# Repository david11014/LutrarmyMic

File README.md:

# LutrarmyMic microphone circuit

# README.md
[English README.en.md](README.en.md)

[繁體中文 README.zh-Hans.md](README.zh-Hans.md)

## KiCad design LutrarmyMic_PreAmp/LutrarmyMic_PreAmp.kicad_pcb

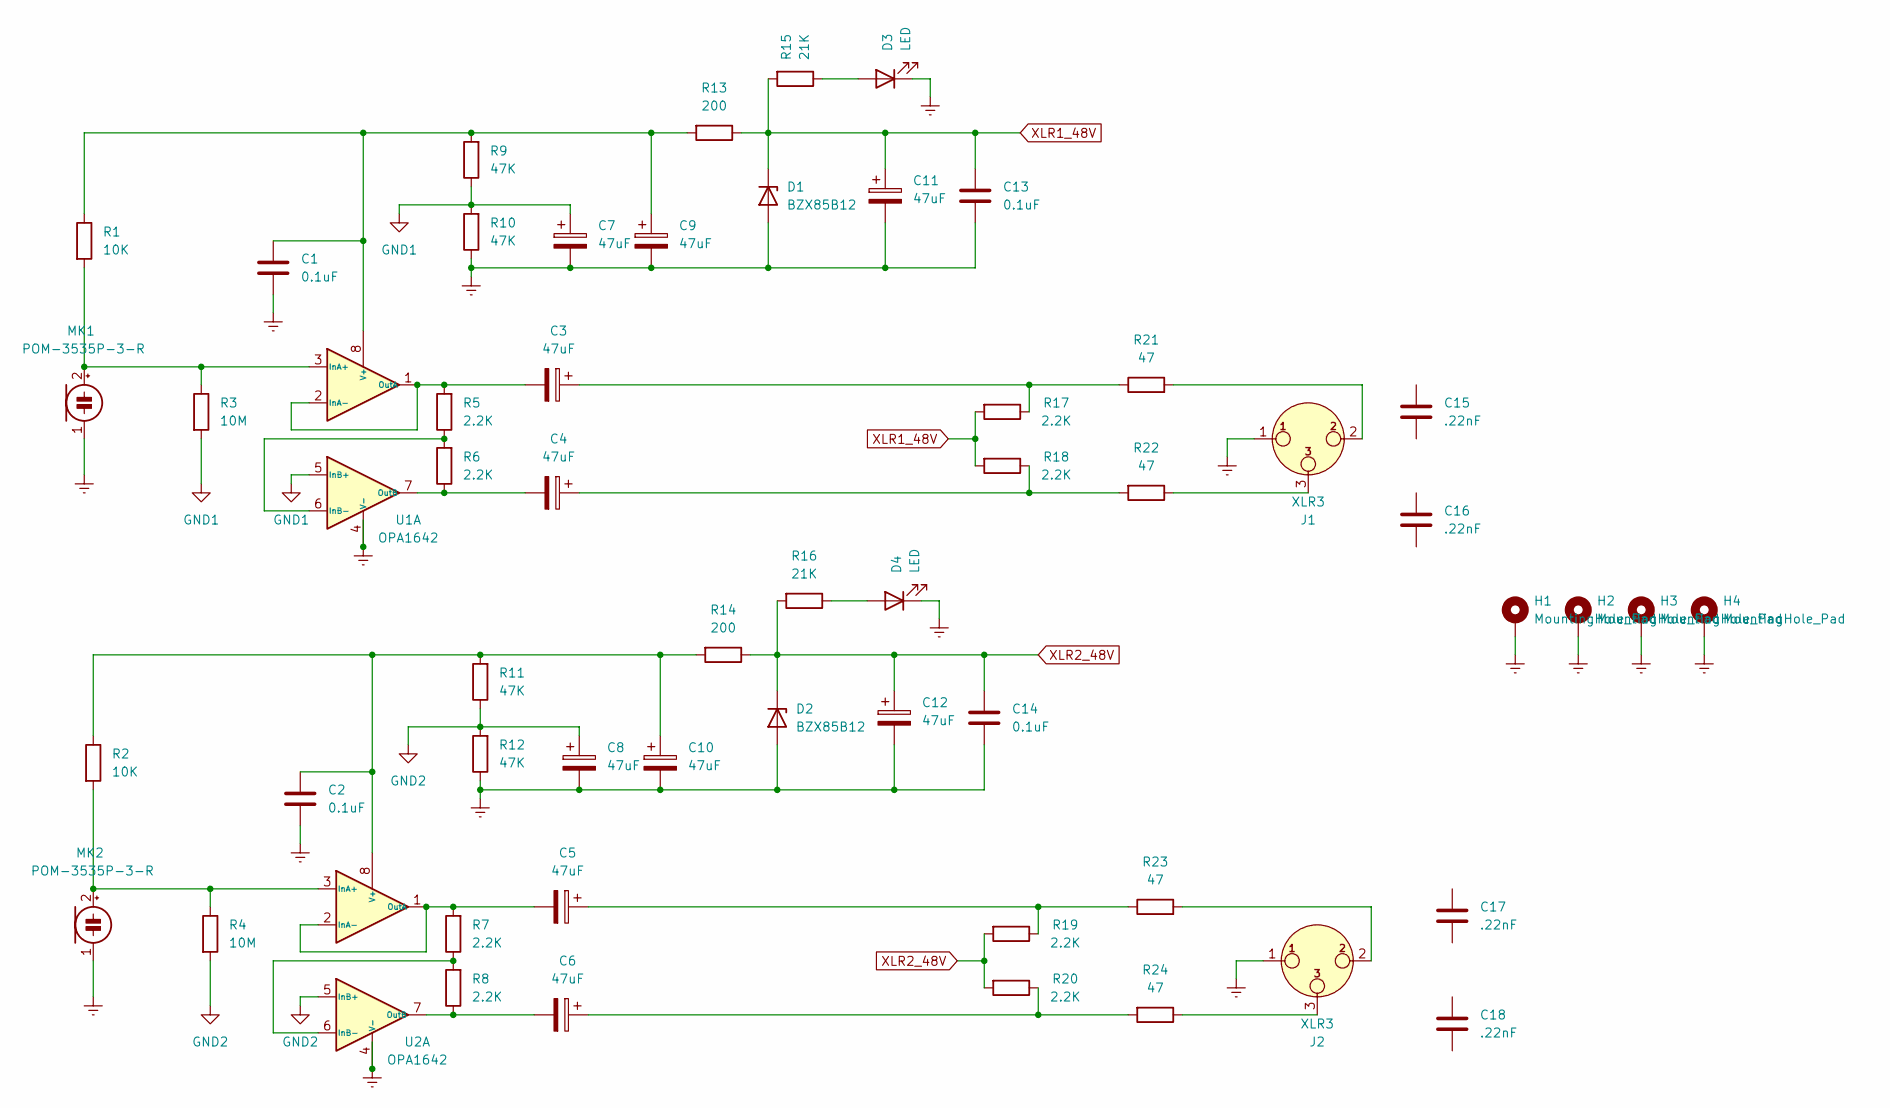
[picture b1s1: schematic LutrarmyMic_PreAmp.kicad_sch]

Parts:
C1, C2, C13, C14: 0.1uF; C_Rect_L7.2mm_W2.5mm_P5.00mm_FKS2_FKP2_MKS2_MKP2
C3, C4, C5, C6, C7, C8, C9, C10, C11, C12: 47uF; CP_Radial_D8.0mm_P3.50mm
C15, C16, C17, C18: .22nF; C_Rect_L7.2mm_W2.5mm_P5.00mm_FKS2_FKP2_MKS2_MKP2
D1, D2: BZX85B12; D_DO-41_SOD81_P10.16mm_Horizontal
D3, D4: LED; LED_D5.0mm_Clear
H1, H2, H3, H4: MountingHole_Pad; MountingHole_3.2mm_M3_DIN965_Pad
J1, J2: XLR3; PinHeader_1x03_P2.54mm_Vertical
MK1, MK2: POM-3535P-3-R; PinHeader_1x02_P2.54mm_Vertical
R1, R2: 10K; R_Axial_DIN0207_L6.3mm_D2.5mm_P10.16mm_Horizontal
R3, R4: 10M; R_Axial_DIN0207_L6.3mm_D2.5mm_P10.16mm_Horizontal
R5, R6, R7, R8, R17, R18, R19, R20: 2.2K; R_Axial_DIN0207_L6.3mm_D2.5mm_P2.54mm_Vertical
R9, R10, R11, R12: 47K; R_Axial_DIN0207_L6.3mm_D2.5mm_P2.54mm_Vertical
R13, R14: 200; R_Axial_DIN0207_L6.3mm_D2.5mm_P10.16mm_Horizontal
R15, R16: 21K; R_Axial_DIN0207_L6.3mm_D2.5mm_P10.16mm_Horizontal
R21, R22, R23, R24: 47; R_Axial_DIN0207_L6.3mm_D2.5mm_P10.16mm_Horizontal
U1, U2: OPA1642; SOIC-8_3.9x4.9mm_P1.27mm

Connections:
Earth: C1.2, C2.2, C7.2, C8.2, C9.2, C10.2, C11.2, C12.2, C13.2, C14.2, D1.2 (A), D2.2 (A), D3.1 (K), D4.1 (K), H1.1, H2.1, H3.1, H4.1, J1.1, J2.1, MK1.1 (-), MK2.1 (-), R10.1, R12.1, U1.4 (V-), U2.4 (V-)
GND1: C7.1, R3.2, R9.1, R10.2, U1.5 (InB+)
GND2: C8.1, R4.2, R11.1, R12.2, U2.5 (InB+)
unnamed: C1.1, C9.1, R1.1, R9.2, R13.2, U1.8 (V+)
unnamed: C3.1, R17.1, R21.1
unnamed: C3.2, R5.2, U1.1 (OutA), U1.2 (InA-)
unnamed: C4.1, R18.1, R22.2
unnamed: C4.2, R6.1, U1.7 (OutB)
unnamed: C5.1, R19.1, R23.1
unnamed: C5.2, R7.2, U2.1 (OutA), U2.2 (InA-)
unnamed: C6.1, R20.1, R24.2
unnamed: C6.2, R8.1, U2.7 (OutB)
unnamed: C2.1, C10.1, R2.1, R11.2, R14.2, U2.8 (V+)
unnamed: D3.2 (A), R15.1
unnamed: D4.2 (A), R16.1
unnamed: J1.2, R21.2
unnamed: J1.3, R22.1
unnamed: J2.2, R23.2
unnamed: J2.3, R24.1
unnamed: MK1.2 (+), R1.2, R3.1, U1.3 (InA+)
unnamed: MK2.2 (+), R2.2, R4.1, U2.3 (InA+)
unnamed: R5.1, R6.2, U1.6 (InB-)
unnamed: R7.1, R8.2, U2.6 (InB-)
XLR1_48V: C11.1, C13.1, D1.1 (K), R13.1, R15.2, R17.2, R18.2
XLR2_48V: C12.1, C14.1, D2.1 (K), R14.1, R16.2, R19.2, R20.2

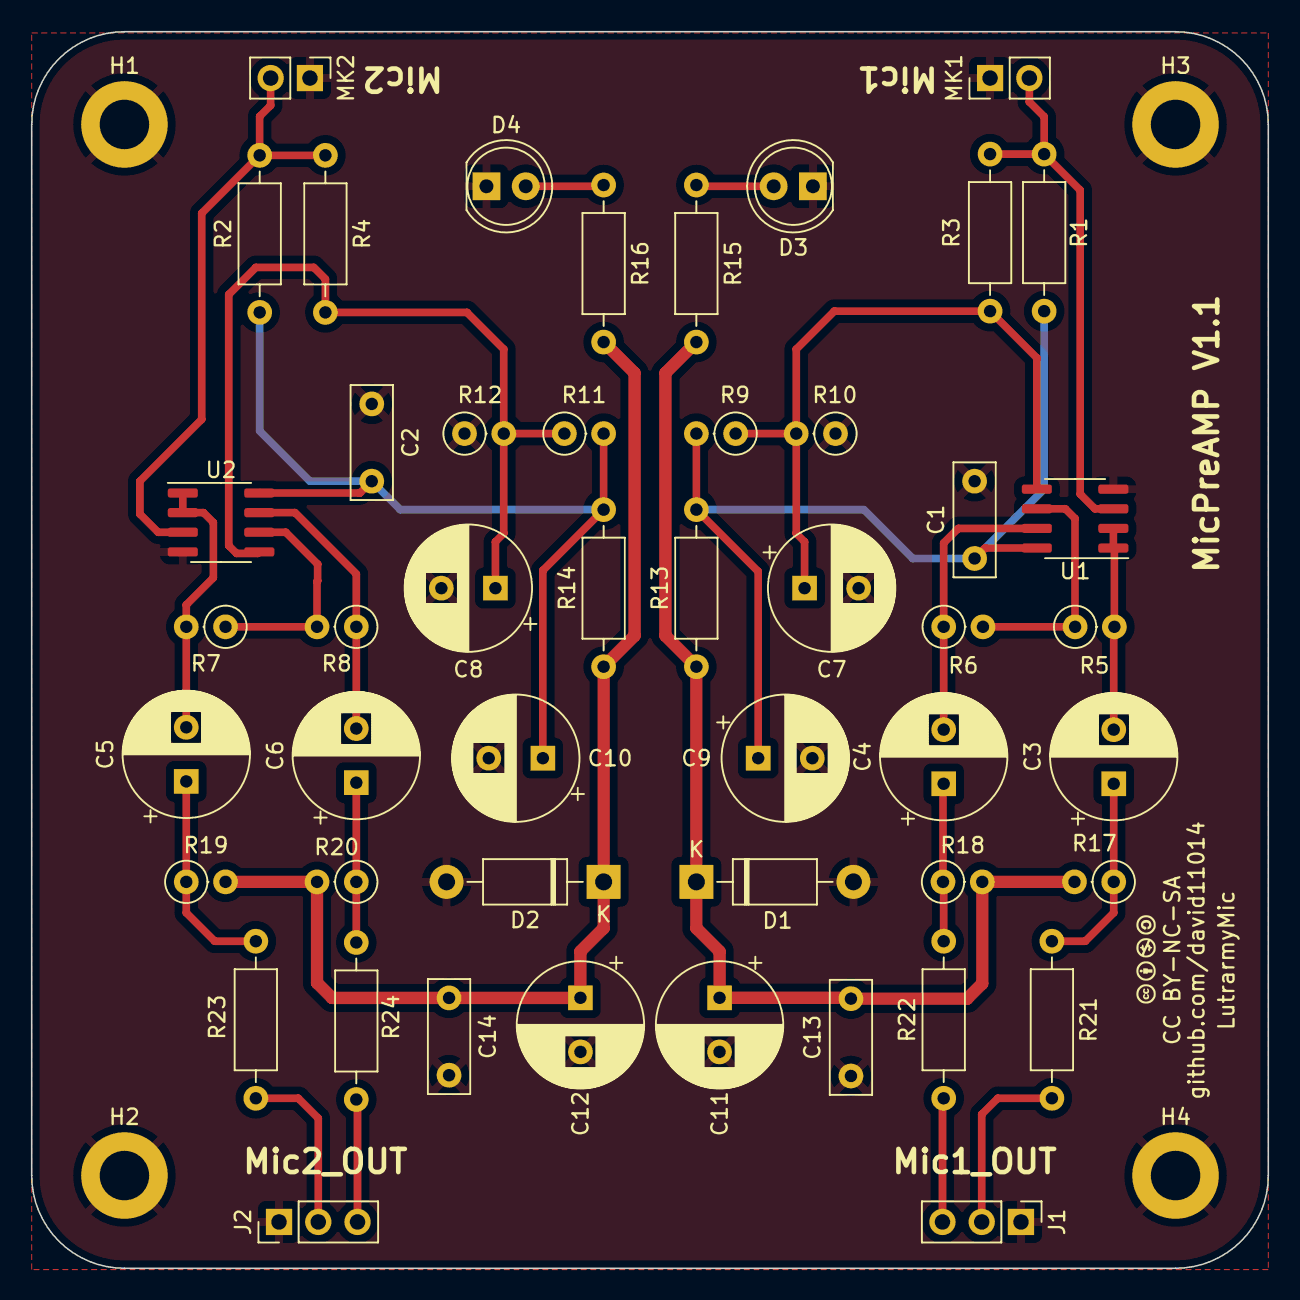
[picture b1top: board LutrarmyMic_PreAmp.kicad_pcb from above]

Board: 2 copper layers, 80.0 x 80.0 mm, 53 parts (0 on the bottom side), 25 nets.

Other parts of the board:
LutrarmyMic: CC-BY-NC-SA

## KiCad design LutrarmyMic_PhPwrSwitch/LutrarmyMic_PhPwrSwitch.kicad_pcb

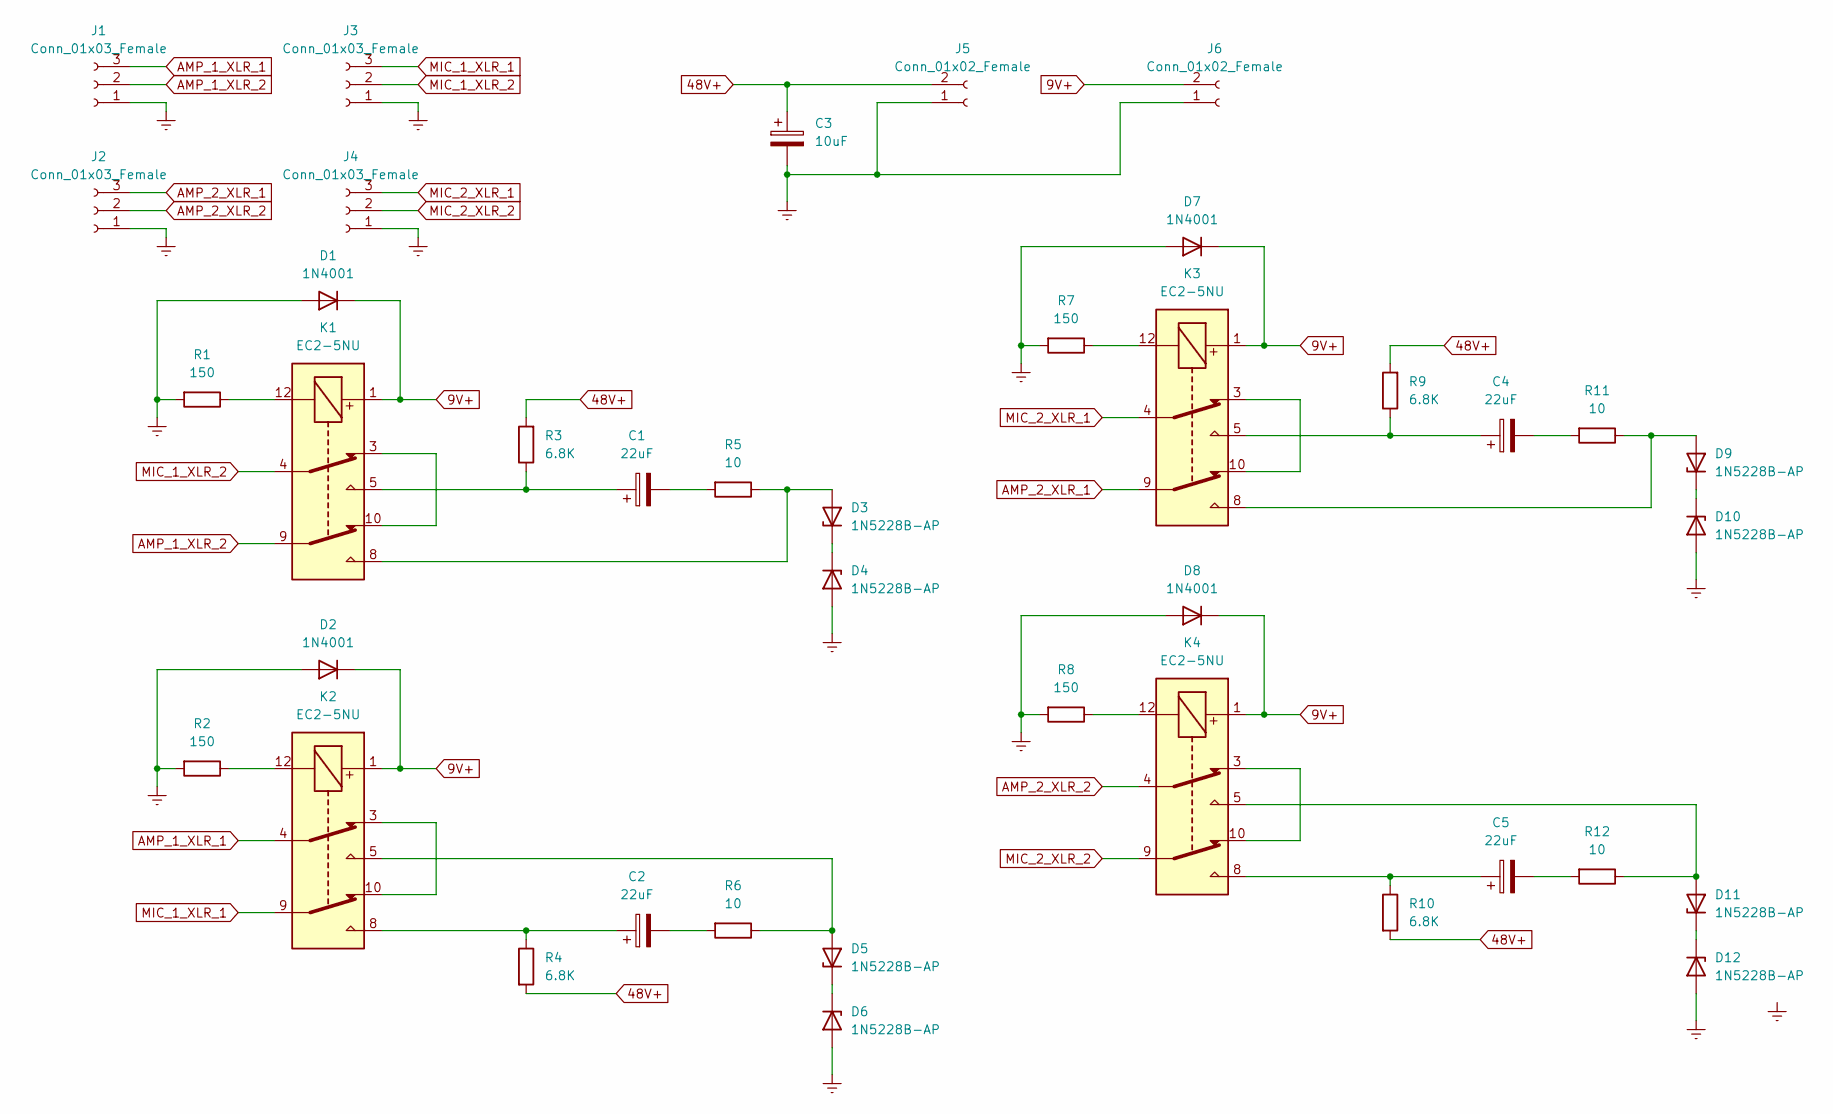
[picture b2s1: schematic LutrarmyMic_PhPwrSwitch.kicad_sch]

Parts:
C1, C2, C4, C5: 22uF; CP_Radial_D6.3mm_P2.50mm
C3: 10uF; CP_Radial_D6.3mm_P2.50mm
D1, D2, D7, D8: 1N4001; D_DO-41_SOD81_P10.16mm_Horizontal
D3, D4, D5, D6, D9, D10, D11, D12: 1N5228B-AP; D_DO-35_SOD27_P7.62mm_Horizontal
J1, J2, J3, J4: Conn_01x03_Female; PinHeader_1x03_P2.54mm_Vertical
J5, J6: Conn_01x02_Female; PinHeader_1x02_P2.54mm_Vertical
K1, K2, K3, K4: EC2-5NU; Relay_DPDT_Kemet_EC2
R1, R2, R7, R8: 150; R_Axial_DIN0207_L6.3mm_D2.5mm_P10.16mm_Horizontal
R3, R4, R9, R10: 6.8K; R_Axial_DIN0207_L6.3mm_D2.5mm_P10.16mm_Horizontal
R5, R6, R11, R12: 10; R_Axial_DIN0207_L6.3mm_D2.5mm_P10.16mm_Horizontal

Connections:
9V+: D1.1 (K), D2.1 (K), D7.1 (K), D8.1 (K), J6.2, K1.1, K2.1, K3.1, K4.1
48V+: C3.1, J5.2, R3.2, R4.2, R9.2, R10.2
AMP_1_XLR_1: J1.3, K2.4
AMP_1_XLR_2: J1.2, K1.9
AMP_2_XLR_1: J2.3, K3.9
AMP_2_XLR_2: J2.2, K4.4
Earth: C3.2, D1.2 (A), D2.2 (A), D4.2 (A), D6.2 (A), D7.2 (A), D8.2 (A), D10.2 (A), D12.2 (A), J1.1, J2.1, J3.1, J4.1, J5.1, J6.1, R1.2, R2.2, R7.2, R8.2
MIC_1_XLR_1: J3.3, K2.9
MIC_1_XLR_2: J3.2, K1.4
MIC_2_XLR_1: J4.3, K3.4
MIC_2_XLR_2: J4.2, K4.9
unnamed: C1.1, K1.5, R3.1
unnamed: C1.2, R5.2
unnamed: C2.1, K2.8, R4.1
unnamed: C2.2, R6.2
unnamed: C4.1, K3.5, R9.1
unnamed: C4.2, R11.2
unnamed: C5.1, K4.8, R10.1
unnamed: C5.2, R12.2
unnamed: D3.1 (K), D4.1 (K)
unnamed: D3.2 (A), K1.8, R5.1
unnamed: D5.1 (K), D6.1 (K)
unnamed: D5.2 (A), K2.5, R6.1
unnamed: D9.2 (A), K3.8, R11.1
unnamed: D9.1 (K), D10.1 (K)
unnamed: D11.1 (K), D12.1 (K)
unnamed: D11.2 (A), K4.5, R12.1
unnamed: K1.3, K1.10
unnamed: K1.12, R1.1
unnamed: K2.3, K2.10
unnamed: K2.12, R2.1
unnamed: K3.3, K3.10
unnamed: K3.12, R7.1
unnamed: K4.3, K4.10
unnamed: K4.12, R8.1

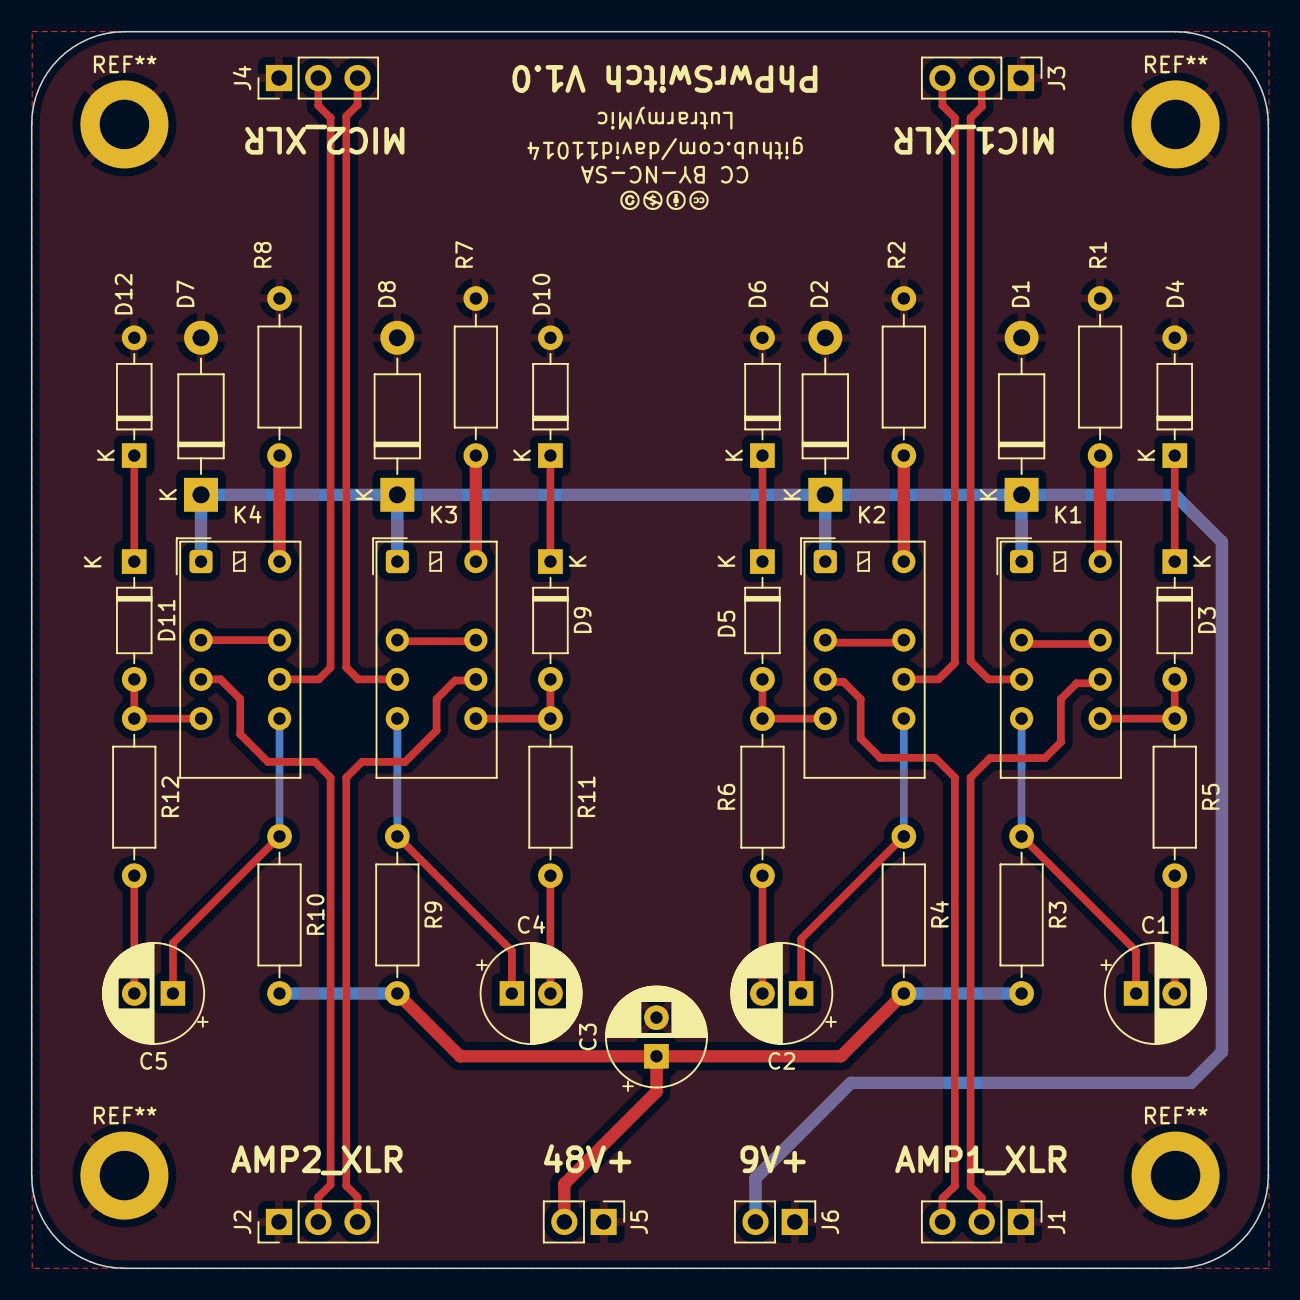
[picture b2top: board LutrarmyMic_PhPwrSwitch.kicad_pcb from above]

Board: 2 copper layers, 80.0 x 80.0 mm, 40 parts (0 on the bottom side), 35 nets.

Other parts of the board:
LutrarmyMic: CC-BY-NC-SA

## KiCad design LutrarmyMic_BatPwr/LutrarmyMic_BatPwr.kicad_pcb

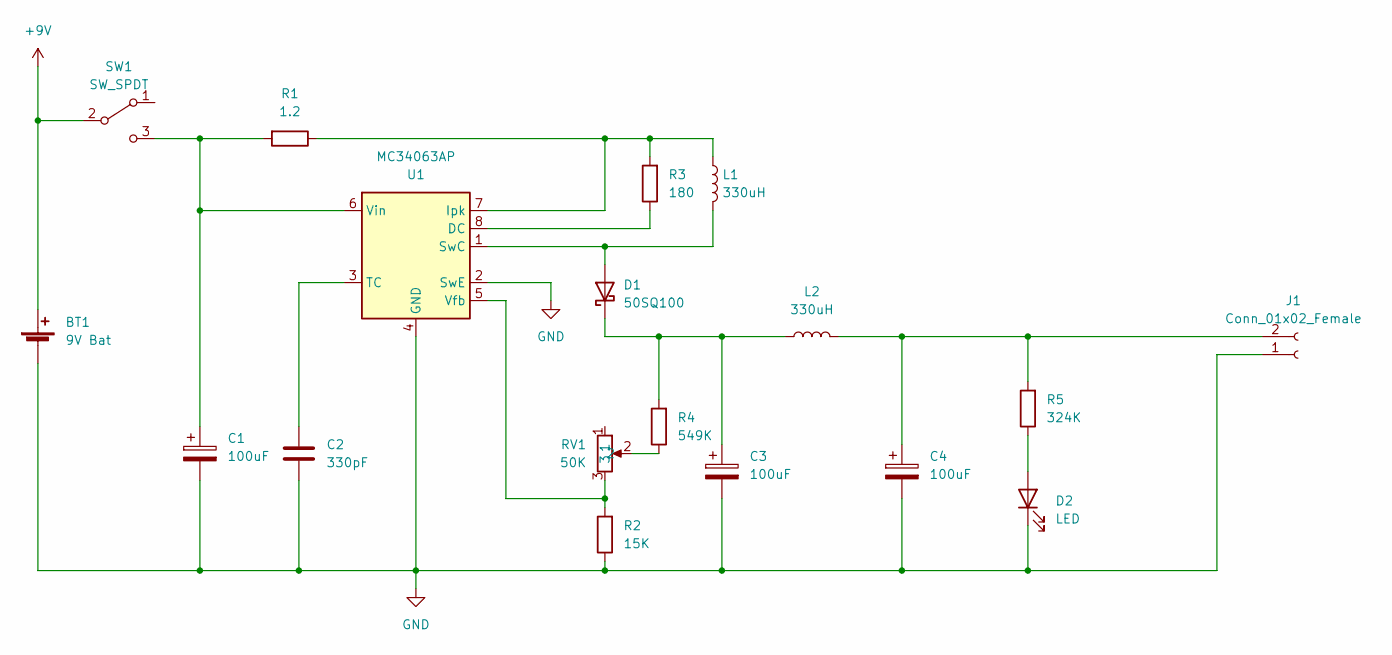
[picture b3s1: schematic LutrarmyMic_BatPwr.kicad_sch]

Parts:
BT1: 9V Bat; PinHeader_1x02_P2.54mm_Vertical
C1, C3, C4: 100uF; CP_Radial_D10.0mm_P5.00mm
C2: 330pF; C_Rect_L7.2mm_W2.5mm_P5.00mm_FKS2_FKP2_MKS2_MKP2
D1: 50SQ100; D_DO-201_P15.24mm_Horizontal
D2: LED; LED_D5.0mm_Clear
J1: Conn_01x02_Female; PinHeader_1x02_P2.54mm_Vertical
L1, L2: 330uH; L_Bourns-SRN8040_8x8.15mm
R1: 1.2; R_Axial_DIN0207_L6.3mm_D2.5mm_P10.16mm_Horizontal
R2: 15K; R_Axial_DIN0207_L6.3mm_D2.5mm_P10.16mm_Horizontal
R3: 180; R_Axial_DIN0207_L6.3mm_D2.5mm_P10.16mm_Horizontal
R4: 549K; R_Axial_DIN0207_L6.3mm_D2.5mm_P10.16mm_Horizontal
R5: 324K; R_Axial_DIN0207_L6.3mm_D2.5mm_P10.16mm_Horizontal
RV1: 50K; Potentiometer_Bourns_3339P_Vertical_HandSoldering
SW1: SW_SPDT; PinHeader_1x03_P2.54mm_Vertical
U1: MC34063AP; DIP-8_W7.62mm

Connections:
+9V: BT1.1 (+), SW1.2 (B)
GND: BT1.2 (-), C1.2, C2.2, C3.2, C4.2, D2.1 (K), J1.1, R2.1, U1.2 (SwE), U1.4 (GND)
unnamed: C1.1, R1.2, SW1.3 (C), U1.6 (Vin)
unnamed: C2.1, U1.3 (TC)
unnamed: C3.1, D1.1 (K), L2.1, R4.2
unnamed: C4.1, J1.2, L2.2, R5.2
unnamed: D1.2 (A), L1.2, U1.1 (SwC)
unnamed: D2.2 (A), R5.1
unnamed: L1.1, R1.1, R3.2, U1.7 (Ipk)
unnamed: R2.2, RV1.3, U1.5 (Vfb)
unnamed: R3.1, U1.8 (DC)
unnamed: R4.1, RV1.2

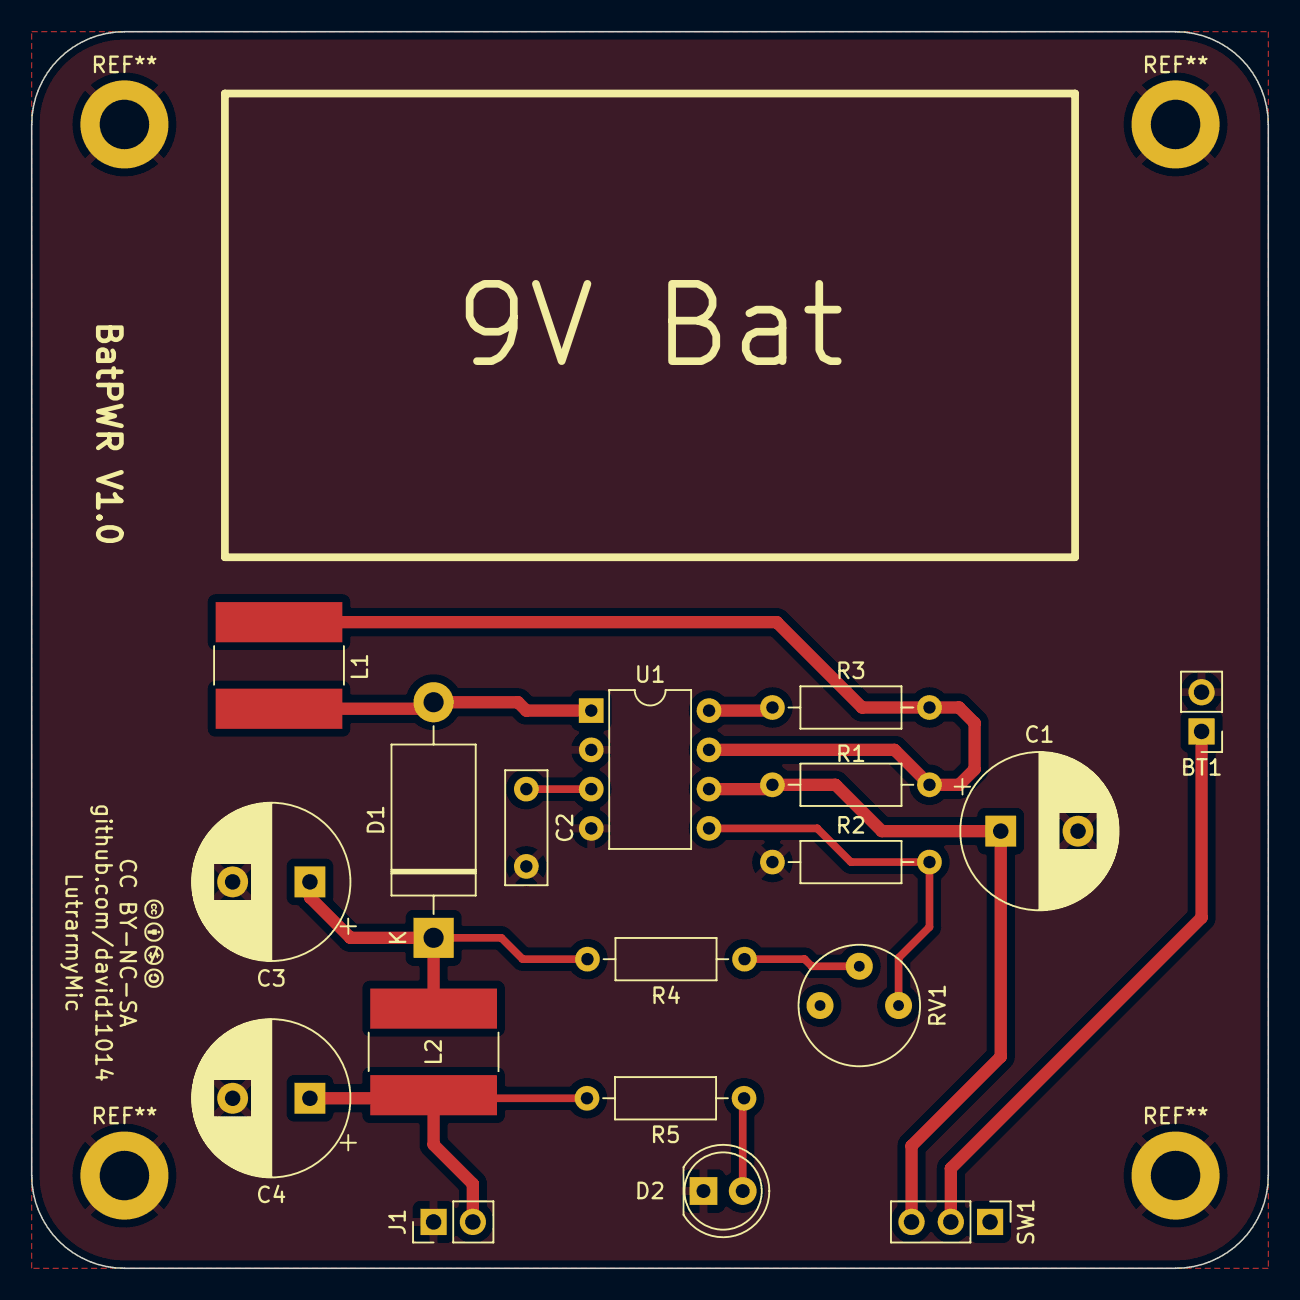
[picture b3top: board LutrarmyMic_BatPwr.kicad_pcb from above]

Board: 2 copper layers, 80.0 x 80.0 mm, 19 parts (0 on the bottom side), 12 nets.

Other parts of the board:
LutrarmyMic: CC-BY-NC-SA

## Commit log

2023-02-25 init commit
2023-02-25 [Add] Add Battery power board
2023-02-25 [Add] Add phantom power switch board
2023-02-25 [Add] Add Mic pre amp board
2023-02-25 [Add] Add gbr and drill file
2023-02-25 [update] update git ignore
2023-02-25 [move] Move file location
2023-02-25 [fix] modify text orientation
2023-04-16 更新最終版 gbr
2023-04-17 [Add] Add README.md
2023-04-22 [Add] Add microphone manual
2023-05-01 [更新] 更新說明書
